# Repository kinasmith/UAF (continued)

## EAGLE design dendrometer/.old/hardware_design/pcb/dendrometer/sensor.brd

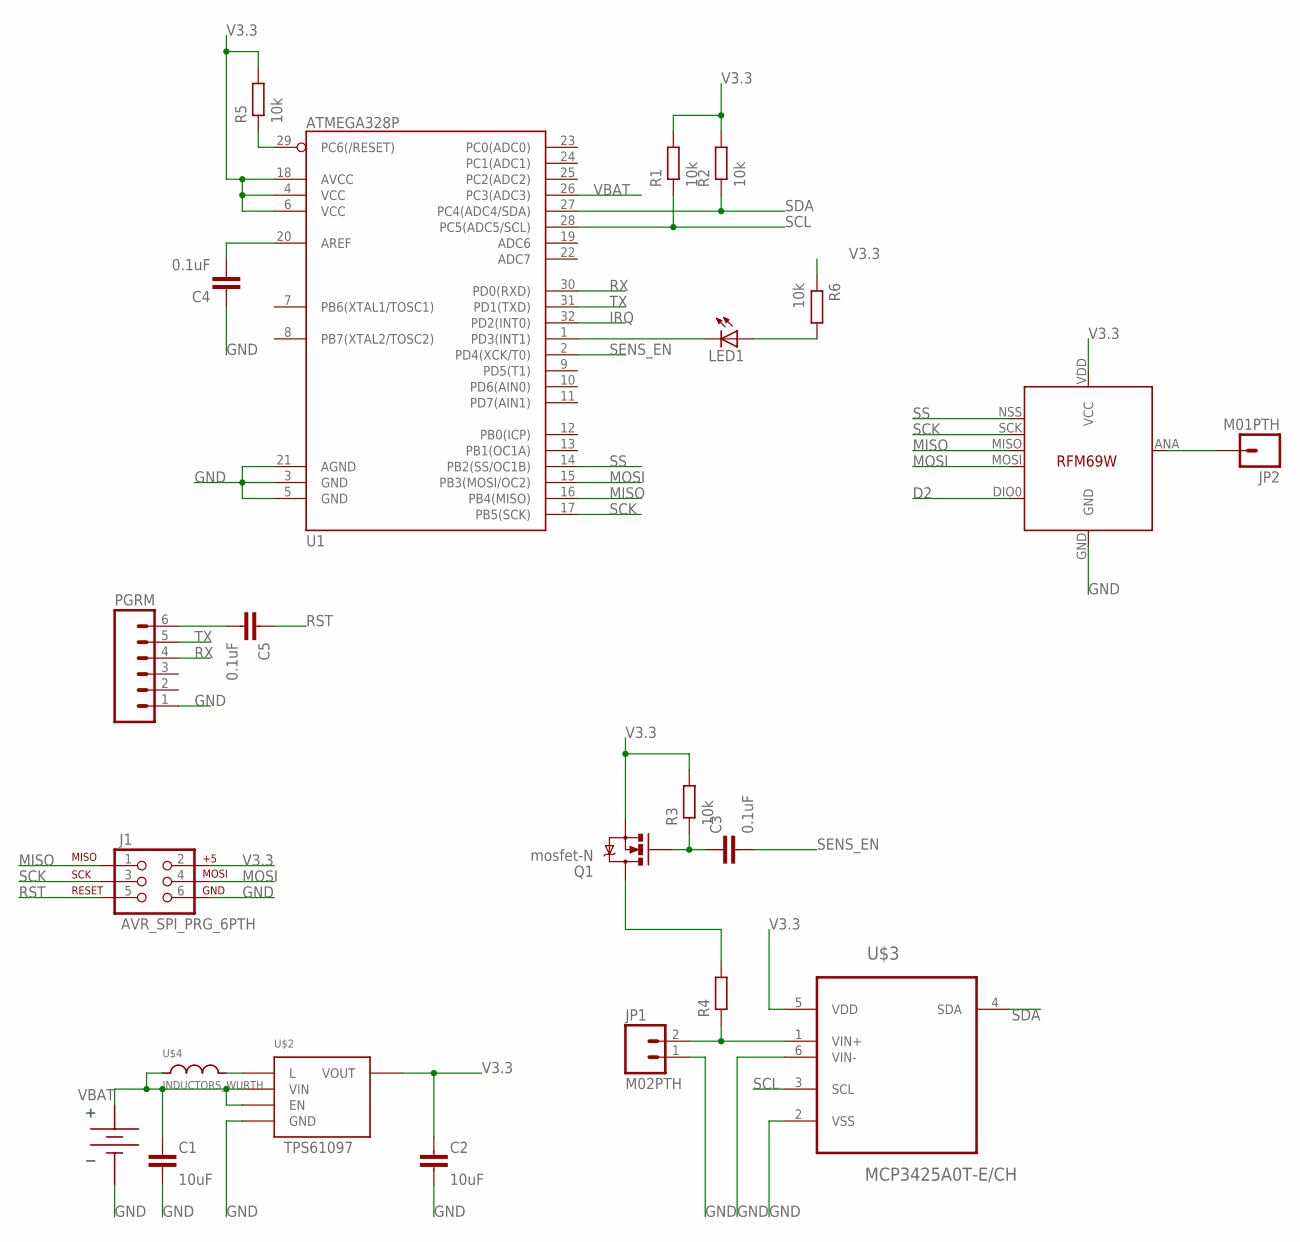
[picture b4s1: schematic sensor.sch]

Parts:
C1, C2: 10uF; C0805-N
C3, C4, C5: 0.1uF; C0603-N
J1: AVR_SPI_PRG_6PTH; 2X3
JP1: M02PTH; 1X02
JP2: M01PTH; 1X01
LED1: LED0603; LED-0603
PGRM: M06LONGPADS; 1X06_LONGPADS
Q1: mosfet-N; SOT23
R1, R2, R3, R5, R6: 10k; R0603-N
R4: RESISTOR0603-N; R0603-N
U1: ATMEGA328P; TQFP32-08
U$1: KEYSTONEAAHOLDER_2CELL
U$2: TPS61097-33; SOT23-5
U$3: MCP3425A0T-E/CH; SOT95P270X145-6N
U$4: INDUCTORS_WURTH; WURTH_10UH_650MA
U$5: RFM69; RFM69W-MINPADS

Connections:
D2: U$5.DIO0
GND: C1.2, C2.2, C4.1, J1.6, JP1.1, PGRM.1, U1.3 (GND), U1.5 (GND), U1.21 (AGND), U$1.P$2 (GND), U$2.P$2 (GND), U$3.2 (VSS), U$3.6 (VIN-), U$5.GND
IRQ: U1.32 (PD2(INT0))
MISO: J1.1, U1.16 (PB4(MISO)), U$5.MISO
MOSI: J1.4, U1.15 (PB3(MOSI/OC2)), U$5.MOSI
unnamed: U$2.P$5 (L), U$4.P$1
unnamed: C3.1, Q1.1 (G), R3.1
unnamed: JP1.2, R4.1, U$3.1 (VIN+)
unnamed: C4.2, U1.20 (AREF)
unnamed: LED1.C, U1.1 (PD3(INT1))
unnamed: Q1.3 (D), R4.2
unnamed: JP2.1, U$5.ANA (ANT)
unnamed: LED1.A, R6.2
unnamed: C5.2, PGRM.6
RST: C5.1, J1.5, R5.1, U1.29 (PC6(/RESET))
RX: PGRM.4, U1.30 (PD0(RXD))
SCK: J1.3, U1.17 (PB5(SCK)), U$5.SCK
SCL: R1.1, U1.28 (PC5(ADC5/SCL)), U$3.3 (SCL)
SDA: R2.1, U1.27 (PC4(ADC4/SDA)), U$3.4 (SDA)
SENS_EN: C3.2, U1.2 (PD4(XCK/T0))
SS: U1.14 (PB2(SS/OC1B)), U$5.NSS (SEL)
TX: PGRM.5, U1.31 (PD1(TXD))
V3.3: C2.1, J1.2, Q1.2 (S), R1.2, R2.2, R3.2, R5.2, R6.1, U1.4 (VCC), U1.6 (VCC), U1.18 (AVCC), U$2.P$4 (VOUT), U$3.5 (VDD), U$5.VDD (VCC)
VBAT: C1.1, U1.26 (PC3(ADC3)), U$1.P$1 (VBAT), U$2.P$1 (VIN), U$2.P$3 (EN), U$4.P$2

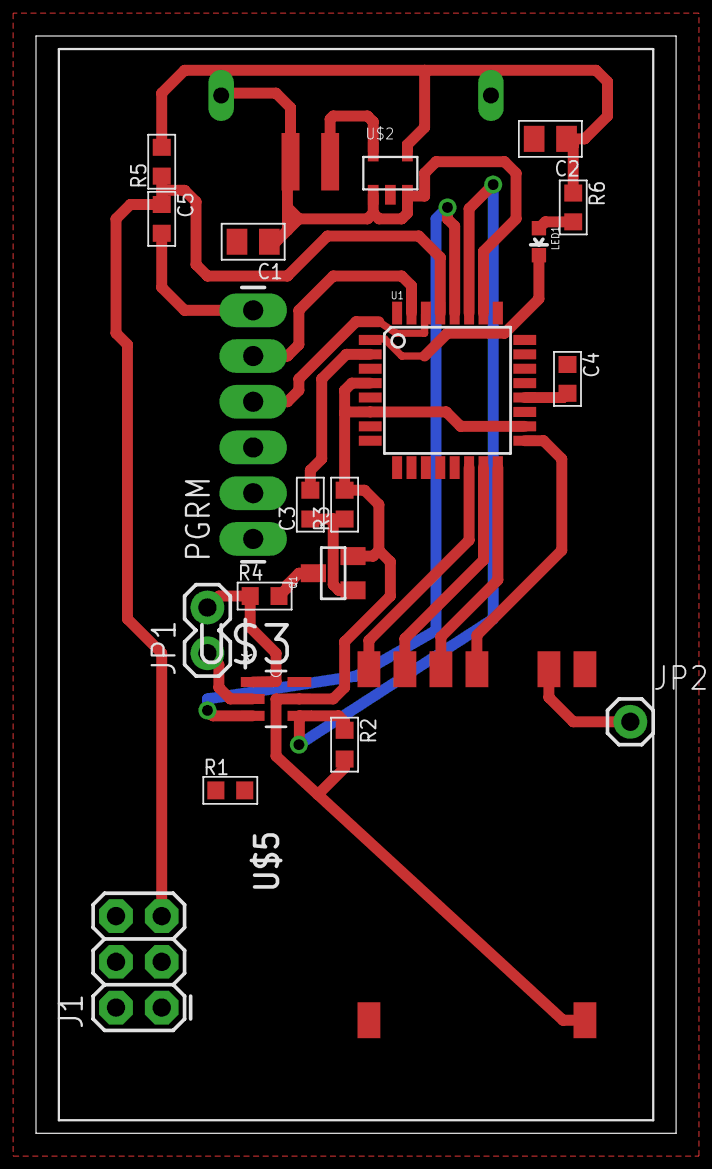
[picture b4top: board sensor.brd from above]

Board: 2 copper layers, 35.6 x 61.0 mm, 23 parts (0 on the bottom side), 22 nets.

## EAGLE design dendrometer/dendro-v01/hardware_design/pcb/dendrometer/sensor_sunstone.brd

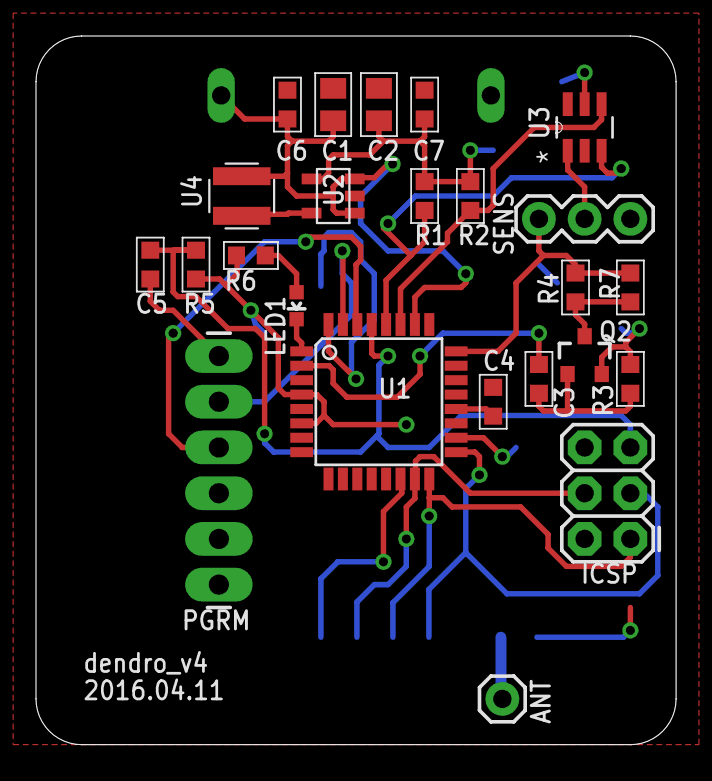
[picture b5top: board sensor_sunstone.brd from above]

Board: 2 copper layers, 35.6 x 39.4 mm, 26 parts (1 on the bottom side), 24 nets.

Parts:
ANT: M01PTH; 1X01
C1, C2: 10uF; C0805-N
C3, C4, C5, C6, C7: 0.1uF; C0603-N
ICSP: AVR_SPI_PRG_6PTH; 2X3
LED1: LED-0603
PGRM: 1X06_LONGPADS
Q2: PFET; SOT23-3
R1, R2, R5, R6: 10k; R0603-N
R3: 2M; R0603-N
R4: DNP; R0603-N
R7: 5.9k; R0603-N
SENS: 1X03
U1: ATMEGA328P; TQFP32-08
U2: TPS61097-33; SOT23-5
U3: MCP3425A0T-E/CH; SOT95P270X145-6N
U4: INDUCTORS_WURTH; WURTH_10UH_650MA
U$1: KEYSTONEAAHOLDER_2CELL
U$5: RFM69; RFM69W-MINPADS

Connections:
G: C3.1, Q2.1, R3.1
GND: C1.2, C2.2, C4.1, C6.2, C7.2, ICSP.6, PGRM.1, SENS.1, U1.3, U1.5, U1.21, U2.P$2, U3.2, U3.6, U$1.P$2, U$5.GND
IRQ: U1.32, U$5.DIO0
MISO: ICSP.1, U1.16, U$5.MISO
MOSI: ICSP.4, U1.15, U$5.MOSI
unnamed: U2.P$5, U4.P$1
unnamed: Q2.3, R4.2, R7.2
unnamed: C4.2, U1.20
unnamed: LED1.C, U1.1
unnamed: SENS.2, U3.1
unnamed: ANT.1, U$5.ANA
unnamed: LED1.A, R6.2
unnamed: C5.2, PGRM.6
RST: C5.1, ICSP.5, R5.1, U1.29
RX: PGRM.4, U1.30
SCK: ICSP.3, U1.17, U$5.SCK
SCL: R1.1, U1.28, U3.3
SDA: R2.1, U1.27, U3.4
SENS_EN: C3.2, U1.2
SS: U1.14, U$5.NSS
TX: PGRM.5, U1.31
V3.3: C2.1, C7.1, ICSP.2, Q2.2, R1.2, R2.2, R3.2, R5.2, R6.1, U1.4, U1.6, U1.18, U2.P$4, U3.5, U$5.VDD
V-EXCITE: R4.1, R7.1, SENS.3, U1.24
VBAT: C1.1, C6.1, U1.26, U2.P$1, U2.P$3, U4.P$2, U$1.P$1

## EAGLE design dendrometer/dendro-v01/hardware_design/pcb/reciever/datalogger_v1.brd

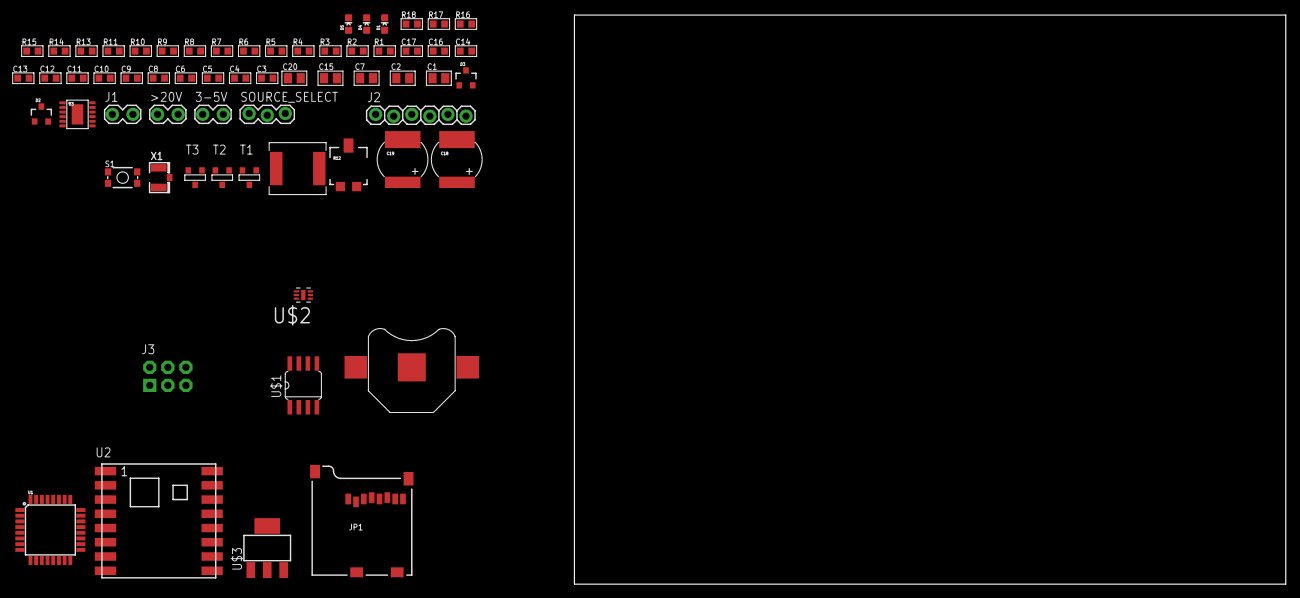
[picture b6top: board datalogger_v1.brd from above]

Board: 2 copper layers, 100.0 x 80.0 mm, 63 parts (0 on the bottom side), 50 nets, no tracks yet.

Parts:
3-5V: 1X02_LOCK
>20V: 1X02_LOCK
BAT1: BATTCON_12MM
C1, C2, C7, C15, C20: 10µF; C0805-N
C3, C4, C16, C17: 1µF; C0603-N
C5: 4.7µF; C0603-N
C6, C8, C9, C10, C11, C12, C13, C14: 0.1µF; C0603-N
C18, C19: 47µF; EN_J2
D1, D4, D5: LED-0603
D2, D3: ZLLS500; SOT23-3
J1: 1X02_LOCK
J2: 1X06_LOCK
J3: AVR_SPI_PRG_6NS; 2X3-NS
JP1: USD-SOCKETNEW; MICRO-SD-SOCKET-PP
L1: 68uH; CR75
R1, R2, R3: 100k; R0603-N
R4, R5, R6, R8, R17, R18: 10k; R0603-N
R7: 470; R0603-N
R9: THERM; R0603-N
R10: 33k; R0603-N
R11: 6.8k; R0603-N
R12: TRIMPOT-5MM-V2
R13: 0.22; R0603-N
R14, R16: 220k; R0603-N
R15: 47k; R0603-N
S1: RST; TACTILE_SWITCH_SMD_4.6X2.8MM
SOURCE_SELECT: 1X03_LOCK
T1, T2, T3: SOT-23
U1: ATMEGA328P_TQFP; TQFP32-08
U2: RFM69HCW; RFM69HCW-XXXS2
U3: LT3652; MSOP-12_GND
U$1: DS3231M; SO08
U$2: LTC3240-3.3VDFN-7; DFN200X200X80-7N
U$3: NCP1117-3.3V-SOT-223; SOT223
X1: ADAFRUIT_U.FL

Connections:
3.3V: C6.1, C7.1, C8.1, C14.1, J3.2, R4.2, R5.2, R6.2, SOURCE_SELECT.2, T1.2, T2.2, U1.4, U1.6, U1.18, U2.13, U$1.2
20V: >20V.2, C1.1, U$3.3
ANT: U2.9, X1.3
BAT_DIV: R10.1, R11.2, U1.23
BAT_EN: T3.3, U1.10
CD: JP1.CD2, U1.13
CHRG: R18.2, U3.4
D_3: U1.1, U$1.3
FLT: R17.2, U3.5
GND: 3-5V.1, >20V.1, BAT1.GND, C1.2, C2.2, C4.1, C5.1, C6.2, C7.2, C8.2, C9.2, C10.1, C11.1, C13.1, C14.2, C15.1, C16.1, C18.-, C19.-, C20.2, D3.1, J1.1, J2.6, J3.6, JP1.GND, JP1.GND1, JP1.GND3, R7.1, R9.1, R11.1, R12.C, R16.2, S1.1, S1.2, U1.3, U1.5, U1.21, U2.1, U2.8, U2.10, U3.13, U$1.5, U$2.1, U$2.7, U$3.1, X1.1, X1.2
INT: U1.32, U2.14
MISO: J3.1, JP1.DO, U1.16, U2.2
MOSI: J3.4, JP1.DI, U1.15, U2.3
unnamed: BAT1.PWR@1, U$1.6
unnamed: C12.1, J2.1
unnamed: C2.1, SOURCE_SELECT.1, U$3.2, U$3.4
unnamed: C11.2, R10.2, T3.1
unnamed: JP1.CD1, R1.1
unnamed: JP1.RSV2, R2.1
unnamed: C17.1, D3.3, L1.P$1, U3.12
unnamed: C10.2, R8.2, T2.1
unnamed: C3.1, U$2.5
unnamed: C3.2, U$2.4
unnamed: C13.2, U1.20
unnamed: L1.P$2, R13.2, U3.10
unnamed: C5.2, SOURCE_SELECT.3, U$2.3
unnamed: R12.B, U3.2
unnamed: JP1.RSV1, R3.1
unnamed: C16.2, U3.6
unnamed: D1.A, U1.2
unnamed: C17.2, D2.3, U3.11
unnamed: R14.1, U3.7
unnamed: R14.2, R15.2, R16.1
unnamed: D1.C, R7.2
unnamed: D4.C, R18.1
unnamed: D5.C, R17.1
unnamed: C9.1, JP1.VCC, R1.2, R2.2, R3.2, T1.1
RST: C12.2, J3.5, R6.1, S1.3, S1.4, U1.29
RX: J2.3, U1.30
SCK: J3.3, JP1.SCLK, U1.17, U2.4
SCL: R4.1, U1.28, U$1.8
SDA: R5.1, U1.27, U$1.7
SD_CS: JP1.CS, U1.12
SD_EN: T1.3, U1.11
SS: U1.14, U2.5
THERM: R8.1, R9.2, U1.24
THERM_EN: T2.3, U1.9
TX: J2.2, U1.31
V_BAT: 3-5V.2, C4.2, C18.+, C19.+, C20.1, D2.1, R13.1, R15.1, T3.2, U3.9, U$2.2, U$2.6
V_SOL: C15.2, D4.A, D5.A, J1.2, R12.A, U3.1, U3.3
